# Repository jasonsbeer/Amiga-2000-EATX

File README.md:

# Amiga 2000 EATX PCB

This is an open source Amiga 2000 PCB in the EATX form factor. EATX is an ATX variant that defines larger PCBs, measuring 12 x 13 inches (305 × 330 mm). These are referred to as Extended ATX, or, EATX (see [Enterprise Electronics Bay Specification](/DataSheets/SSI%20EEB%202011%201.0.1.pdf)). The length of Zorro II cards and the abundance of components on the Amiga 2000 makes EATX the best choice for this project.

There are one-to-one board replacement projects for the Amiga 2000, but none to change the layout to meet current form factor standards. In addition, the Amiga 2000 made use of connectors and custom parts that are no longer commercially manufactured. This often requires parts to be pulled from existing machines. As such, this project will make use of only actively supported components when possible.

In addition to a new board replacement option, I believe the ubiquitous EATX standard will bring additional interest to the Amiga as a hobbyist and retro-computing option. At the time or writting this, the Amiga operating system is still actively developed and supported. In addition, there is a substantial database of existing software and hardware add-on options and an active community.

Discord: https://discord.gg/NU7SPYfNFj

## Project Status

### Revision 3.1 is the current production board.

**Known Issues**: See Issues tab.

Revision 3.0 can be found [here](https://github.com/jasonsbeer/Amiga-2000-EATX/tree/Rev-3.0).  
Revision 2.2 can be found [here](https://github.com/jasonsbeer/Amiga-2000-EATX/tree/Rev-2.2).  
Revision 1.2.1 can be found [here](https://github.com/jasonsbeer/Amiga-2000-EATX/tree/Rev-1.2.1).  

If you are interested in a brief history of this project, check out the [Gallery page](/Gallery.md).

## User Guide and Considerations
Review [this information](userguide.md) to ensure a smooth and happy experience when assembling an Amiga 2000 EATX system. It will answer many questions and inform you as to the physical requirements of the Amiga 2000 EATX PCB, various Amiga plug in cards, etc.

## Ordering PCBs
See information [here](PCB.md). 

## BOM and Assembling the Amiga 2000 EATX PCB

See information [here](AssemblyNotes.md).

## Changes from the original Amiga 2000

The Amiga 2000 EATX is derived from the Commodore Amiga 2000 Rev 6.2 schematics. To my knowledge, all known Rev 6.x PCB updates are included in this project. 

### Video
The DB23 video connector has been removed in favor of the HD15 connector. One of the goals of this project is to avoid parts that are not commercially available. The D-Sub 23 connector is a prime example. They are not stocked at popular electronic supply houses. Thus, the change to the widely available HD15 connector. Analog red, green, blue, HSYNC or COMPSYNC (jumper selectable), and VSYNC are supplied using the VGA standard pin out configuration. Other external video port signals are not supplied. Any VGA cable can be used to supply the video signal to a VGA monitor or conversion box supporting the 15KHz standard. 

The internal video slot is complete with all signals.

The external composite video jack has been removed.

### Memory
The original 256Kx4 DRAMs have been replaced by a single SRAM. The Amiga 2000 EATX supports 1 or 2 MB of chip memory, depending on your Agnus version. See additional information in the [assembly notes](AssemblyNotes.md).

### Audio Output
The left/right RCA jacks of the Amiga have been replaced by a 3.5mm stereo audio jack.

### Disk Drive Support
Internally, any Amiga compatable double density disk drive or properly configured Gotek floppy emulator is supported. Up to two internal disk drives may be connected to the internal floppy connector. Up to two external disk drives may be connected via a user supplied adapter cable.

### ISA Slots
The number of 16 bit ISA slots has been reduced to three. This was done to provide additional space on the board. Support for ISA cards via a Bridgeboard is unchanged from the Amiga 2000.

### Serial Port
The internal (infernal) serial port has been removed. The external serial port is present with all signals.

### PCB Layout
For obvious reasons, it was necessary to move components relative to one another. Zorro slots occupy slot positions 1-5, overlapping with ISA slots in the first 3 positions. The video slot occupies the sixth slot position on the board.  The CPU slot occupies position 7. It is possible to have every slot position populated simultaneously.

### ATX Power
ATX 24-pin power supplies are supported with -5V being supplied on board via a voltage regulator. The original Amiga 2000 power supply is not supported.

### External Reset Switch
The computer can be reset via CTRL-Amiga-Amiga on an Amiga keyboard or via the reset switch found on EATX computer cases.

### Real Time Clock
There are two real time clock (RTC) options beginning with revision 2.x. You can install the original Amiga 2000 RTC, which is based on the MSM6242, or a simplified RTC based on the RTC-62423. The MSM6242 requires more components and will need to be trimmed to dial in the correct clock speed. The RTC-62423 has a built in crystal and does not need adjustment, but is less accurate over time. In the Amiga, the RTC is written and read by 4 address and 4 data lines. There are no direct "modern" replacements for the type of bus connected RTC used in the Amiga. As such, the RTC chip you choose is among the legacy IC's that must be obtained. 

### TICK
The TICK timing signal on the original Amiga 2000 was supplied by the power supply and is a 50 or 60Hz signal determined by the mains power in use. ATX power supplies do not supply a TICK or any AC signal. Starting with Revision 2.2, a TICK Header (J300) was added to support independently generated TICK signals in the event your desired configuration demands this. The factory default setting supplies a TICK signal from the Agnus _VSYNC signal, which is suitable for most configurations. See [TICK HEADER](/AssemblyNotes.md#tick-header-j300) for more details and considerations. All revisions 2.1 and lower use the Agnus _VSYNC signal.

## What has not changed?
### Most External Ports
The keyboard, joystick, mouse, parallel, and serial ports are all present and function as they did in the Amiga 2000. The parallel, serial, mouse, and joystick ports are stacked DB9 and DB25 connectors, respectively. The Amiga keyboard port remains a DIN5 connector.

### Zorro II Slots
There are no changes to the Zorro II slots.

### Kickstart ROM
For now, the Kickstart ROM remains the original 27C400. These are no longer made, but are easy to find. In addition, this allows the use of an original Commodore Kickstart mask ROM. Revision 1.2 added support for 1MB (27C800) and 2MB (27C160) EPROMs for custom Kickstart ROMs.

### Everything Else
If something is not specifically mentioned, you should expect it to be unchanged in function or component from the original Amiga 2000.

## Revision History

Rev 3.1 **CURRENT PRODUCTION REVISION**
1. Various fixes (see closed issues flagged for Revision 3.1)
2. Changed SRAM back to +5V part
3. Added copper pours to top and bottom layer
4. Updated to KiCAD 8.0

Rev 3.0
1. Various fixes (see closed issues flagged for Revision 3.0)
2. Changed SRAM to 5V tolerant 3.3V part (lack of availability of +5V part)
3. Removed almost all signal traces from power planes
4. Swapped position of U801 and U899 and brought related components to front of board
5. Updated to KiCAD 7.0

Rev. 2.2  
1. Added TICK header (J300)
2. Cleaned up some odd routing that went back to the early revisions of this project
3. Changed footprint of CN300 to support more part options

Rev 2.1
1. Changed footprint of U9000 to offer more part options
2. Added U207 to buffer VSYNC and HSYNC signals
3. Relocated Zorro termination components
4. Added additional component values to silk screen
5. Moved many traces to the external layers

Rev 2.0
1. Supports both Agnus 8372A and certain Agnus 8375 part numbers on the same board
2. Added external floppy drive header
3. Support for two real-time clock options
4. Cleaned up the schematics

Rev 1.2.1 (First Production Release)
1. Added some missing component values to the silk screen, where there was room
2. Moved VIDIOT over to make additional room for coprocessor cards

Rev 1.2
1. Fixed traces on the keyboard connector (error on the C= schematic)
2. Added missing _COPCFG trace
3. Deleted some extra traces that were not needed
4. Added HSYNC/COMPSYNC selection jumper
5. Cleaned up parts of the schematics
6. Widened U801 footprint (RTC62423 is wider than the standard SOIC package)
7. Added support for 1 and 2 MB Kickstart ROMs (512k still supported)
8. Added some space around the external ports...they were crowded

Rev 1.1
1. New ATX on/off circuit
2. Modified SRAM circuit
3. Added case fan header
4. Fixed U100 and other footprints
5. Moved some components
6. Cleaned up silk screen

Rev 1.0
1. Adjusted postion of slots and several other components
2. Moved ATX On/Off circuit to back of board

Rev 0 - Prototype board
   
## Acknowledgments
kr239 - for the Amiga 500 DRAM replacement project inspiration and LIV2 and texneus for the modifications used in this project

iansbremmer - Amiga IC KiCad footprints - https://github.com/iansbremner/ReAmiga-3000---KiCAD

texneus - ATX ON/OFF and AC TICK circuit

DarrenHD - Pics and measurements of the Amiga 3000 video slot bracket adapter - https://eab.abime.net/showthread.php?t=106928

Chucky - Amiga Diagrom...a priceless diagnostic tool - http://www.diagrom.com/

floppie209 - For testing the Rev 3.0 board.

Everyone that made the Amiga possible.

**Last Updated 02-JUN-2024**

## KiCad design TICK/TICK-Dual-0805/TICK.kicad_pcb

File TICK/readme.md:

# TICK Generator Boards

Included here are two options ([9VAC](#9vac-tick-generator) and [Crystal Oscillator](#crystal-oscillator-tick-generator)) for generating an independent TICK signal for the Amiga 2000 EATX. These could be used in other projects needing a replacement TICK generator, such as adding an ATX power supply to an original big box Amiga. Both options are very simple circuits, small in size, and designed to be placed directly on J300 of the Amiga 2000 EATX Rev 2.2 and greater.

For more information on the Amiga 2000 EATX TICK and considerations, see [HERE](/README.md#tick) and [HERE](/AssemblyNotes.md#tick-header-j300)

Gerber files can be found [HERE](/Gerber).

## 9VAC TICK Generator
TICK signals are generated from the frequency of the mains power in use. This means 50 or 60 Hz, depending on where you are in the world. ATX power supplies, such as used by the Amiga 2000 EATX, supply neither a TICK nor AC signal of any type. Thus, it is necessary to create our own with a small circuit suitable for any mains frequency. In this case, we are using a 9VAC wall wart transformer to supply an AC signal based on the mains of the local power grid. Using 9VAC reduces the risk associated with powering such a device directly from mains while allowing us a more traditional TICK signal. Note that the AC TICK board will continue to receive power and function (to some extent) while the wall wart is plugged in, even when the Amiga 2000 EATX is turned off. You may wish to use a switched outlet or simply unplug the wall wort when not in use. Ensure alignment of pin 1 on the Amiga 2000 EATX with pin 1 on the 9VAC TICK board. See [BOM](#bom).

Image 1. The 9VAC TICK generator board on the Amiga 2000 EATX.

Image 2. A 60Hz TICK signal from the 9VAC TICK Generator.

## Crystal Oscillator TICK Generator
Like many modern components, we can also generate an accurate TICK signal with a crystal oscillator. The advantage of this is that we have an entirely self-contained circuit that does not rely on external power sources to drive the frequency. This circuit is a single board, though slighly more complex than the AC TICK circuit, powered directly by the Amiga 2000 EATX. To ensure the correct 50 or 60 Hz frequency, we use the crystal that matches the desired frequency of the video standard your machine is configured to. This circuit is based on the original published by [Michael Schulz](https://aminet.net/package/docs/hard/Mix_and_Tick). Ensure alignment of pin 1 on the Amiga 2000 EATX with pin 1 on the crystal oscillator TICK board. See [BOM](#bom).

Image 3. The crystal oscillator TICK generator board on the Amiga 2000 EATX.

Image 4. A 50Hz TICK signal from the crystal oscillator TICK Generator.

## Dual Oscillator TICK Generator
Submitted by kavanoz and sparxUK, this TICK generator is based on the crystal oscillator TICK board but can be set to either PAL or NTSC via the on-board jumper. The passives have been reduced to the 0805 footprint. The BOM and assembly files can be found with the Gerber files in the [Gerber](/Gerber) folder.

Image 5. Dual oscillator TICK board on the Amiga 2000 EATX.

## BOM
**Table 1.** 9VAC BOM

Reference|Value|Footprint|Notes
-|-|-|-
C1|0.22uF|1206|
D1|1N4148|SOD-323|
R1|4.7k|1206|See Footnote*
R2|4.7k|1206|
Q1|MMBT3904|SOT-23|
CN1|6 Pin Female Header|2.54mm Pitch|
CN2|Barrel Jack||Optional
-|9VAC Wall Wart Transformer||

*It is possible to use transformer output values other than 9VAC. For 6VAC, R1 does not change. For 12VAC or 16VAC transformers, R1 = 10k. For 20VAC or 24VAC transformers, R1 = 22k. These values are untested, so care should be taken when opting to use transformer values greater than 9VAC.

**Table 2.** Crystal Oscillator BOM
Reference|Value|Footprint|Notes
-|-|-|-
C1|6.8pF|1206|
C2|6.8pF|1206|
C3|0.1uF|1206|
C4|0.1uF|1206|
R1|10M|1206|
R2|100k|1206|
U1|74HC4060|16-SOIC|
U2|74HC73|14-SOIC|
Y1|3.93216MHZ|HC-49/U|60Hz (NTSC)
Y1|3.2768MHz|HC-49/U|50Hz (PAL)
CN1|6 Pin Female Header|2.54mm Pitch|

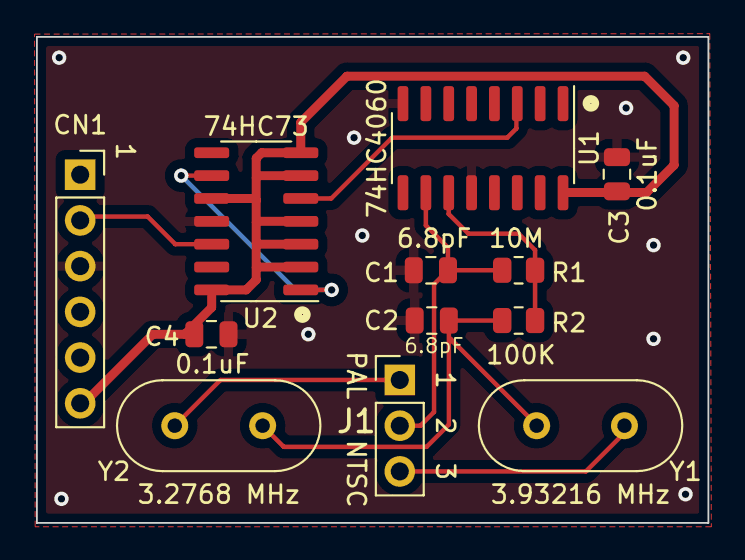
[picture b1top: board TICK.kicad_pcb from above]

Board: 2 copper layers, 37.3 x 27.0 mm, 12 parts (0 on the bottom side), 10 nets.

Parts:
C1, C2: 6.8pF; C_0805_2012Metric
C3, C4: 0.1uF; C_0805_2012Metric
CN1: To_Amiga; PinSocket_1x06_P2.54mm_Vertical
J1: Conn_01x03_Male; PinHeader_1x03_P2.54mm_Vertical
R1: 10M; R_0805_2012Metric
R2: 100K; R_0805_2012Metric
U1: 74HC4060; SOIC-16_3.9x9.9mm_P1.27mm
U2: 74HC73; SOIC-14_3.9x8.7mm_P1.27mm
Y1: 3.93216 MHz; Crystal_HC49-U_Vertical
Y2: 3.2768 MHz; Crystal_HC49-U_Vertical

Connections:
+5V: C3.1, C4.2, CN1.6, U1.16 (V+), U2.2 (~R), U2.3 (K), U2.4 (VCC), U2.6 (~R), U2.7 (J), U2.10 (K), U2.14 (J)
/TBASE: CN1.2, U2.12 (Q)
GND: C1.2, C2.2, C3.2, C4.1, CN1.3, U1.8 (GND), U1.12 (MR), U2.11 (GND)
unnamed: C1.1, J1.2, R1.1, U1.10 (RTC)
unnamed: C2.1, R2.2, Y1.2, Y2.1
unnamed: J1.1, Y2.2
unnamed: J1.3, Y1.1
unnamed: R1.2, R2.1, U1.11 (RS)
unnamed: U1.3 (Q13), U2.5 (C)
unnamed: U2.1 (C), U2.9 (Q)
